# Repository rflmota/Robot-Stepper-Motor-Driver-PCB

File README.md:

# Robot Stepper Motor Driver PCB

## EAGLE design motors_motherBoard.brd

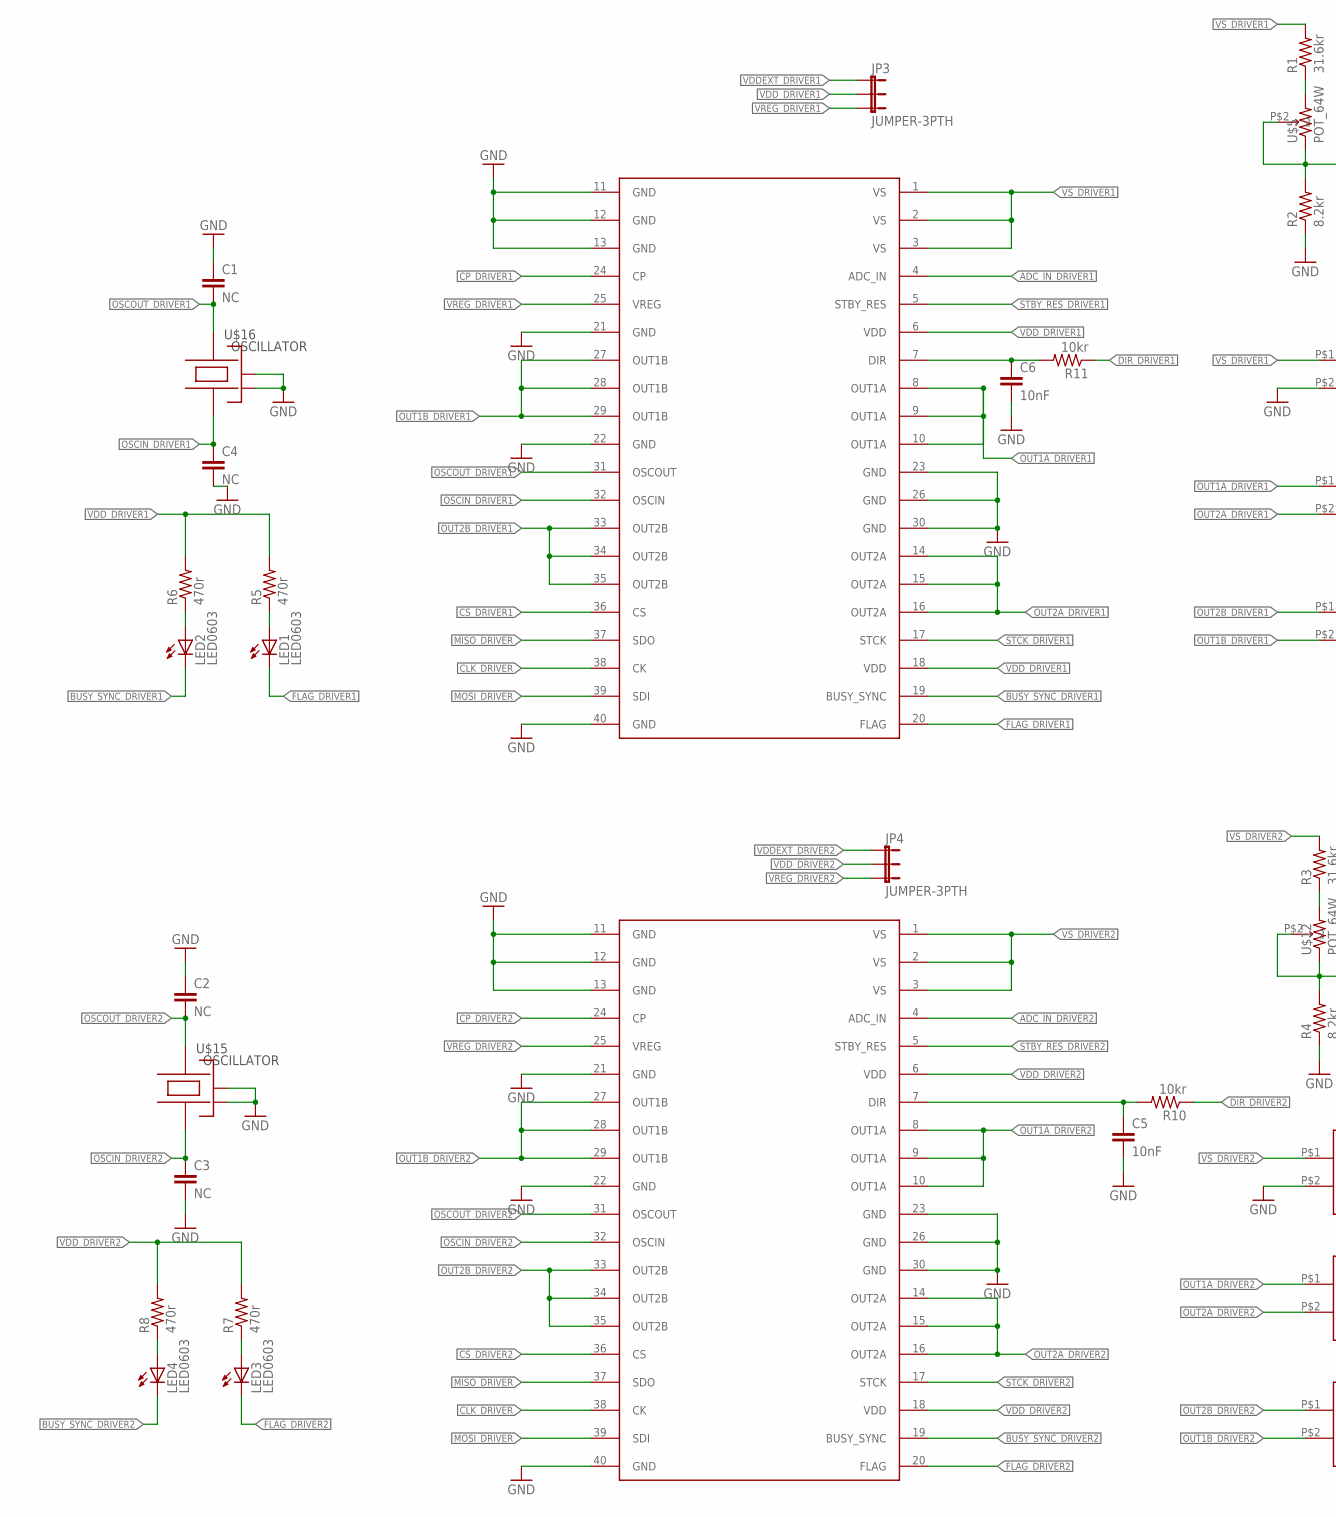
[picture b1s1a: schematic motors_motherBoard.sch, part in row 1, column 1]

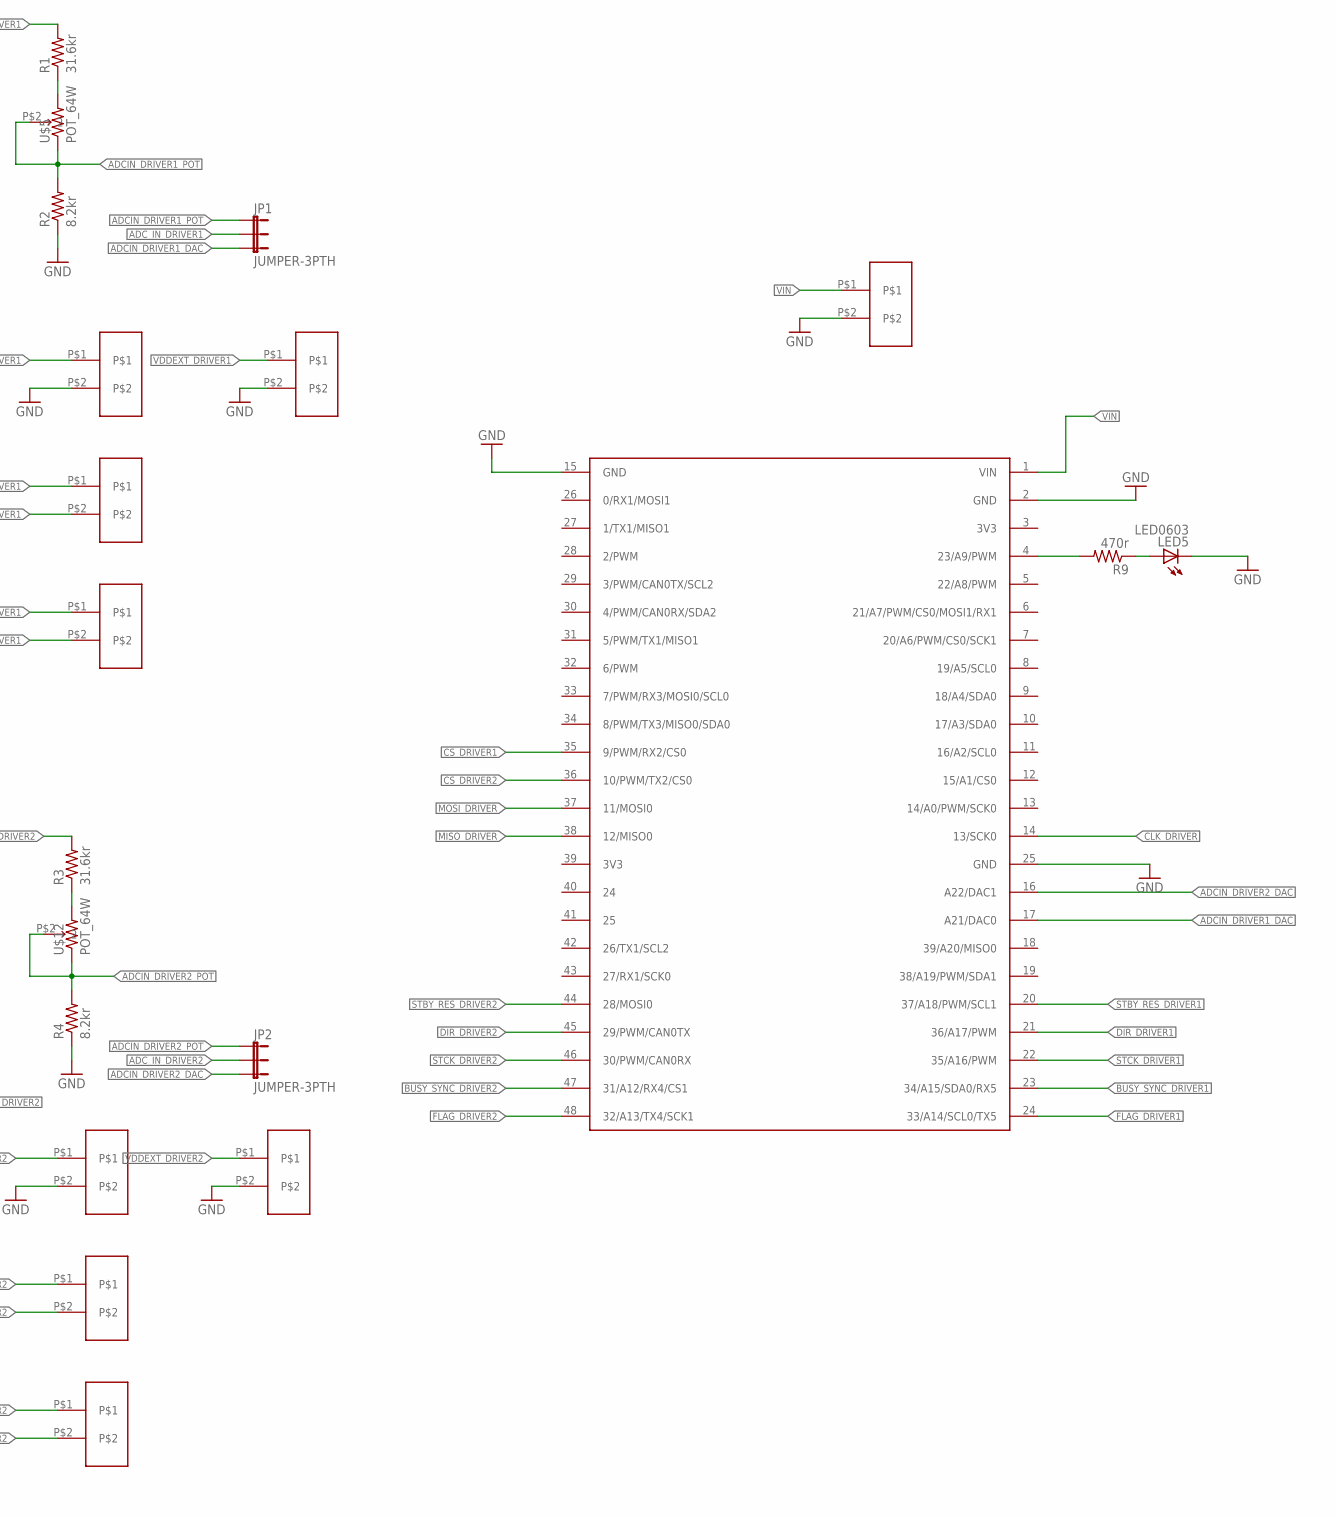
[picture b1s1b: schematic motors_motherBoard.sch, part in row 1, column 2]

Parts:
C1, C2, C3, C4: NC; 0603-CAP
C5, C6: 10nF; 0603-CAP
JP1, JP2, JP3, JP4: JUMPER-3PTH; 1X03
LED1, LED2, LED3, LED4, LED5: LED0603; 0603-LED
R1, R3: 31.6kr; 0603-RES
R2, R4: 8.2kr; 0603-RES
R5, R6, R7, R8, R9: 470r; 0603-RES
R10, R11: 10kr; 0603-RES
U$1, U$2: MOTORDRIVER_BASE_ADAPTER
U$3: TEENSY_BASE_ADAPTER
U$4, U$6, U$7, U$8, U$9, U$10, U$11, U$13, U$14: SCREW_CON_2POLES
U$5, U$12: POT_64W
U$15, U$16: OSCILLATOR; OSCILLATOR_3.2X2.5

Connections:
ADCIN_DRIVER1_DAC: JP1.3, U$3.17 (A21/DAC0)
ADCIN_DRIVER1_POT: JP1.1, R2.2, U$5.P$1 (1), U$5.P$2 (2)
ADCIN_DRIVER2_DAC: JP2.3, U$3.16 (A22/DAC1)
ADCIN_DRIVER2_POT: JP2.1, R4.2, U$12.P$1 (1), U$12.P$2 (2)
ADC_IN_DRIVER1: JP1.2, U$2.4 (ADC_IN)
ADC_IN_DRIVER2: JP2.2, U$1.4 (ADC_IN)
BUSY_SYNC_DRIVER1: LED2.C, U$2.19 (BUSY_SYNC), U$3.23 (34/A15/SDA0/RX5)
BUSY_SYNC_DRIVER2: LED4.C, U$1.19 (BUSY_SYNC), U$3.47 (31/A12/RX4/CS1)
CLK_DRIVER: U$1.38 (CK), U$2.38 (CK), U$3.14 (13/SCK0)
CP_DRIVER1: U$2.24 (CP)
CP_DRIVER2: U$1.24 (CP)
CS_DRIVER1: U$2.36 (CS), U$3.35 (9/PWM/RX2/CS0)
CS_DRIVER2: U$1.36 (CS), U$3.36 (10/PWM/TX2/CS0)
DIR_DRIVER1: R11.1, U$3.21 (36/A17/PWM)
DIR_DRIVER2: R10.1, U$3.45 (29/PWM/CAN0TX)
FLAG_DRIVER1: LED1.C, U$2.20 (FLAG), U$3.24 (33/A14/SCL0/TX5)
FLAG_DRIVER2: LED3.C, U$1.20 (FLAG), U$3.48 (32/A13/TX4/SCK1)
GND: C1.P$1 (1), C2.P$1 (1), C3.P$2 (2), C4.P$2 (2), C5.P$2 (2), C6.P$2 (2), LED5.C, R2.1, R4.1, U$1.11 (GND), U$1.12 (GND), U$1.13 (GND), U$1.21 (GND), U$1.22 (GND), U$1.23 (GND), U$1.26 (GND), U$1.30 (GND), U$1.40 (GND), U$2.11 (GND), U$2.12 (GND), U$2.13 (GND), U$2.21 (GND), U$2.22 (GND), U$2.23 (GND), U$2.26 (GND), U$2.30 (GND), U$2.40 (GND), U$3.2 (GND), U$3.15 (GND), U$3.25 (GND), U$7.P$2, U$9.P$2, U$11.P$2, U$13.P$2, U$14.P$2, U$15.2 (GND), U$15.4 (GND), U$16.2 (GND), U$16.4 (GND)
MISO_DRIVER: U$1.37 (SDO), U$2.37 (SDO), U$3.38 (12/MISO0)
MOSI_DRIVER: U$1.39 (SDI), U$2.39 (SDI), U$3.37 (11/MOSI0)
unnamed: R3.1, U$12.P$3 (3)
unnamed: R1.1, U$5.P$3 (3)
unnamed: LED2.A, R6.1
unnamed: LED1.A, R5.1
unnamed: LED4.A, R8.1
unnamed: LED3.A, R7.1
unnamed: LED5.A, R9.1
unnamed: R9.2, U$3.4 (23/A9/PWM)
unnamed: C6.P$1 (1), R11.2, U$2.7 (DIR)
unnamed: C5.P$1 (1), R10.2, U$1.7 (DIR)
OSCIN_DRIVER1: C4.P$1 (1), U$2.32 (OSCIN), U$16.1
OSCIN_DRIVER2: C3.P$1 (1), U$1.32 (OSCIN), U$15.1
OSCOUT_DRIVER1: C1.P$2 (2), U$2.31 (OSCOUT), U$16.3
OSCOUT_DRIVER2: C2.P$2 (2), U$1.31 (OSCOUT), U$15.3
OUT1A_DRIVER1: U$2.8 (OUT1A), U$2.9 (OUT1A), U$2.10 (OUT1A), U$6.P$1
OUT1A_DRIVER2: U$1.8 (OUT1A), U$1.9 (OUT1A), U$1.10 (OUT1A), U$4.P$1
OUT1B_DRIVER1: U$2.27 (OUT1B), U$2.28 (OUT1B), U$2.29 (OUT1B), U$8.P$2
OUT1B_DRIVER2: U$1.27 (OUT1B), U$1.28 (OUT1B), U$1.29 (OUT1B), U$10.P$2
OUT2A_DRIVER1: U$2.14 (OUT2A), U$2.15 (OUT2A), U$2.16 (OUT2A), U$6.P$2
OUT2A_DRIVER2: U$1.14 (OUT2A), U$1.15 (OUT2A), U$1.16 (OUT2A), U$4.P$2
OUT2B_DRIVER1: U$2.33 (OUT2B), U$2.34 (OUT2B), U$2.35 (OUT2B), U$8.P$1
OUT2B_DRIVER2: U$1.33 (OUT2B), U$1.34 (OUT2B), U$1.35 (OUT2B), U$10.P$1
STBY_RES_DRIVER1: U$2.5 (STBY_RES), U$3.20 (37/A18/PWM/SCL1)
STBY_RES_DRIVER2: U$1.5 (STBY_RES), U$3.44 (28/MOSI0)
STCK_DRIVER1: U$2.17 (STCK), U$3.22 (35/A16/PWM)
STCK_DRIVER2: U$1.17 (STCK), U$3.46 (30/PWM/CAN0RX)
VDDEXT_DRIVER1: JP3.1, U$13.P$1
VDDEXT_DRIVER2: JP4.1, U$11.P$1
VDD_DRIVER1: JP3.2, R5.2, R6.2, U$2.6 (VDD), U$2.18 (VDD)
VDD_DRIVER2: JP4.2, R7.2, R8.2, U$1.6 (VDD), U$1.18 (VDD)
VIN: U$3.1 (VIN), U$14.P$1
VREG_DRIVER1: JP3.3, U$2.25 (VREG)
VREG_DRIVER2: JP4.3, U$1.25 (VREG)
VS_DRIVER1: R1.2, U$2.1 (VS), U$2.2 (VS), U$2.3 (VS), U$7.P$1
VS_DRIVER2: R3.2, U$1.1 (VS), U$1.2 (VS), U$1.3 (VS), U$9.P$1

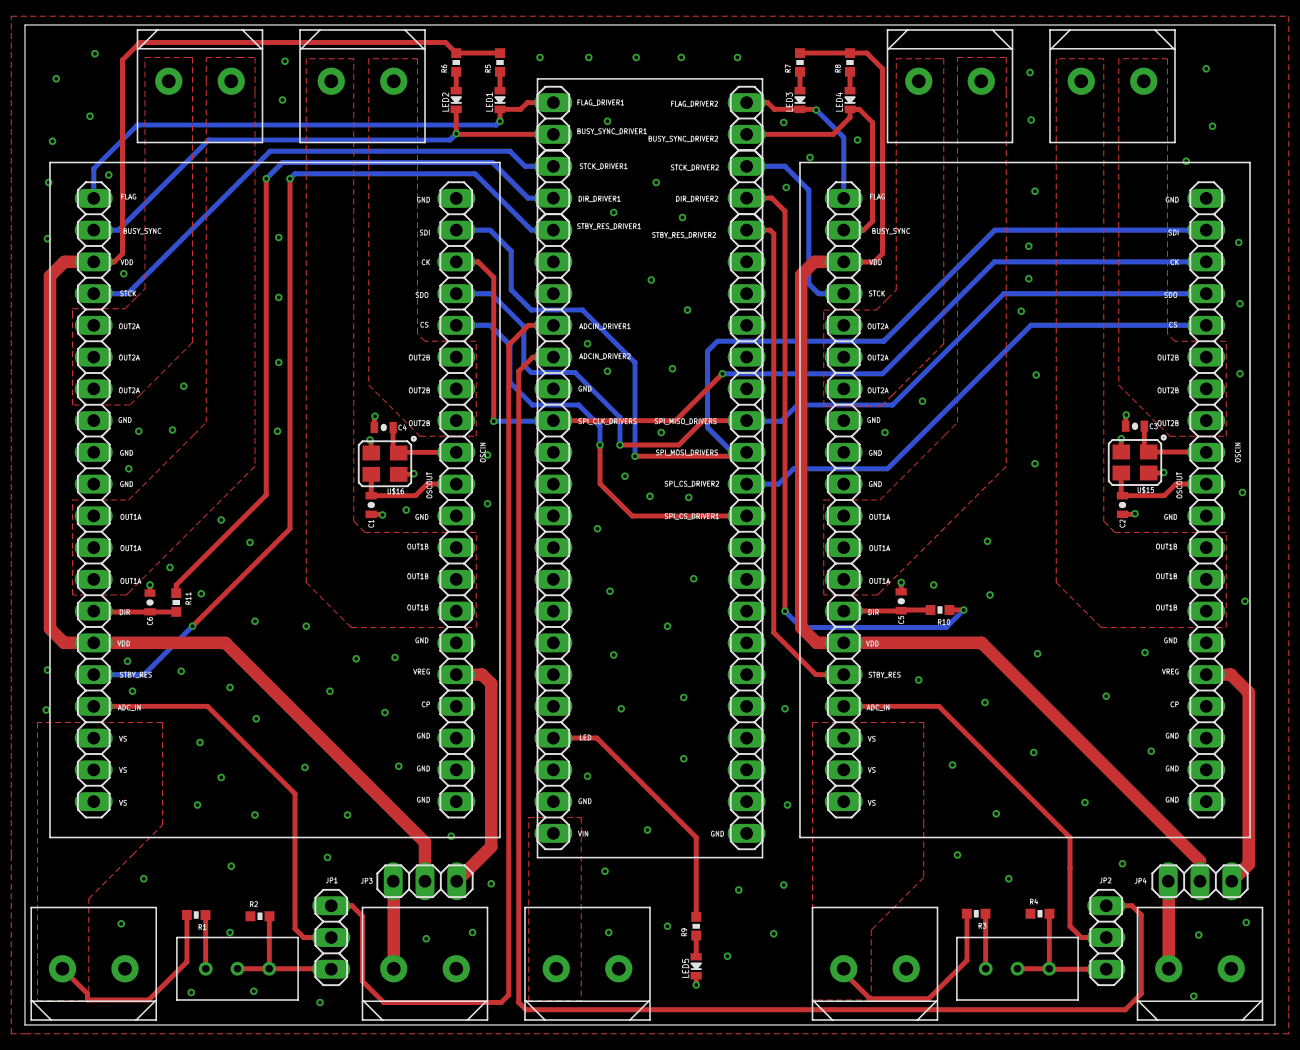
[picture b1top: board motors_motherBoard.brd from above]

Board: 2 copper layers, 100.0 x 80.0 mm, 42 parts (0 on the bottom side), 53 nets.

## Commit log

2018-12-11 Added README
